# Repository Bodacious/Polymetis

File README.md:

# Polymetis

A 60-key, low-profile keyboard in the exact HHKB Professional 2 layout, with a one-piece 6.25u space bar, Gateron KS-33 low-profile switches on hot-swap sockets, an RP2040 on the board, and RMK firmware with Vial.

The layout is drawn to scale in [`docs/layout.html`](docs/layout.html): keys are coloured by the finger that presses them, and the modifiers are dark grey to match the body. A rotatable concept model is in [`docs/concept.html`](docs/concept.html).

## At a glance

| | |
|---|---|
| Keys | 60, HHKB Professional 2 |
| Bottom row | 1.25u gap, Alt, Cmd 1.5u, Space 6.25u, Cmd 1.5u, Alt, 2.5u gap |
| Switches | Gateron KS-33 Low Profile 2.0, linear (Red) |
| Sockets | Gateron KS-2P02B01-02 hot-swap |
| Stabilisers | one Gateron low-profile plate-mounted 6.25U under the space bar |
| Controller | RP2040 on the board, USB-C |
| Top plate | 1.2 mm FR4, 14.00 mm switch cut-outs |
| Bottom plate | 1.6 mm FR4 with a notch for the USB-C receptacle |
| Frame | 5.3 mm, printed |
| Firmware | RMK with Vial; base layer and the HHKB Fn layer, plus track controls |

The HHKB Professional 2 bottom row has a 6u space bar and a 1.5u gap on the left. Polymetis uses a 6.25u space bar, which low-profile keycap sets include, and takes the extra 0.25u from the left gap. The right-hand bottom keys sit clear of the RP2040, reset pad and boot button. The space bar is centred 6.875u from the left edge, which is where the boundary between the two index fingers falls when averaged over the three letter rows.

## Parts

| Part | Quantity | Notes |
|---|---|---|
| Gateron KS-33 Low Profile 2.0 switch, linear (Red) | 60 | 3.0 mm total travel, 1.7 mm to actuation, 50 gf (Gateron drawing); chosen for short travel |
| Gateron KS-2P02B01-02 low-profile hot-swap socket | 60 | JLCPCB lists it as C18212911; zero stock in October 2026, so plan to solder them by hand |
| Gateron low-profile plate-mounted stabiliser, 6.25U (KS-57B623T) | 1 | sold in a 60% set with four 2U; only the 6.25U is used |
| Main PCB, 1.6 mm, with JLCPCB assembly | 1 | files in `jlcpcb/` |
| Top plate, 1.2 mm FR4 | 1 | `top-plate/` |
| Bottom plate, 1.6 mm FR4 | 1 | `bottom-plate/` |
| Printed middle frame, 5.3 mm | 1 | `case/polymetis-frame.stl` |
| Rubber feet | 4 | tall enough for your USB-C plug: half the plug's thickness minus 2 mm (see `docs/checks/pre-order-verification.md`) |
| M2 screws and nuts | 8 | through top plate, frame and bottom plate (8.1 mm stack) |
| Low-profile keycaps with a cross (MX) stem | 60 | 51 × 1u, 4 × 1.5u, 2 × 1.75u, 2 × 2.25u, 1 × 6.25u |

When ordering FR4 plates from JLCPCB, pay the small extra to leave the order number off.

Gateron's datasheets for the switch, socket and stabilisers are in [`docs/datasheets/`](docs/datasheets/), with a note of what each drawing confirms.

## Stack height

All figures in millimetres, from Gateron's drawings unless marked.

| Layer | Thickness | Source |
|---|---|---|
| Top plate | 1.20 | KS-33 drawing: plate 1.20 ± 0.05 |
| Gap, plate to PCB | 1.30 | KS-33 drawing: plate top to PCB top 2.50 ± 0.05 |
| PCB | 1.60 | |
| Tallest part below the PCB | 2.16 | flash U4, SOIC-8 208-mil, maximum height (Winbond W25Q16JV datasheet) |
| Clearance | 0.24 | |
| **Frame** | **5.30** | gap + PCB + tallest part + clearance |
| Bottom plate | 1.60 | |

The hot-swap sockets are 1.87 below the PCB (KS-2P02B01-02 drawing, ± 0.05) and the reset button 1.5 (XKB TS-1187A); the flash chip is the tallest at 1.95 nominal, 2.16 maximum. The exception is the USB-C receptacle (HRO TYPE-C-31-M-12), which stands 3.26 above the PCB surface it is mounted on. It sits in the frame's USB opening, and the bottom plate has a matching 16 × 13.7 mm notch below it. The stabiliser housing reaches 0.35 below the PCB through its slots.

The frame cavity is cut from the PCB outline plus 0.3 mm.

## The space bar stabiliser

The Gateron 6.25U stabiliser housings reach 3.25 mm below the top plate, more than the 1.30 mm gap, so the PCB has a slot under each housing. Gateron does not publish PCB slot dimensions. The slots here are 6.5 × 16 mm at 100 mm spacing, the size Keebio uses for this stabiliser, centred on the stems and offset 1.8 mm towards the wire-hook side. The top plate uses Gateron's recommended cut-out (6.00 × 12.50 mm housing openings with a 1.70 mm notch, and the 2.50 mm wire groove between them), measured from Gateron's drawing.

The space bar row is only 7.9 mm from the PCB's front edge, so the stabiliser is turned with its notch and wire hooks towards the back of the keyboard; the plate cut-out and the PCB slots both face that way.

**Test-fit before ordering the main PCB.** Order the top plate first (it is cheap), fit the stabiliser and a KS-33 switch, and check that the housings and wire sit within the PCB slot outline in `pcb/local.pretty/STAB_Gateron_LP_6.25U_PCB.kicad_mod`. Enter and left Shift have no stabilisers by design.

## Assembly notes

- Fit the stabiliser in the top plate with its notch towards the back of the keyboard.
- The bottom plate's "Polymetis" text faces outwards (down). The USB notch then lines up with the frame's USB opening at the back right.
- Sockets go on the underside of the PCB, the same side as the RP2040 and diodes. Switches go in from the top through the plate.

## Firmware

RMK 0.5 with Vial, in `firmware/`. Layer 0 is the HHKB Professional 2 base layer. Layer 1 replicates the HHKB Professional 2 Fn layer, plus track controls and a bootloader key on keys the HHKB leaves unused. Hold Fn (right of right Shift) and press

| Keys | Function |
|---|---|
| Esc | Power |
| `1` … `=` | F1 … F12 |
| `\` / `` ` `` | Insert / Delete |
| Tab | Caps Lock |
| `I` `O` `P` | Print Screen, Scroll Lock, Pause |
| `[` | Up |
| Backspace | Backspace |
| `A` `S` `D` | Volume down, volume up, mute |
| `F` | Eject (the HHKB's Mac-mode key) |
| `H` `J` | Keypad `*`, keypad `/` |
| `K` `L` | Home, Page Up |
| `;` `'` | Left, right |
| Enter | Keypad Enter |
| `N` `M` | Keypad `+`, keypad `-` |
| `,` `.` | End, Page Down |
| `/` | Down |
| `Z` `X` `C` | Previous track, play/pause, next track (not on the HHKB) |
| `B` | Bootloader, for flashing (not on the HHKB) |

Any key can be remapped live from the Vial app (or vial.rocks in Chrome), with no rebuild.

### Building and flashing

1. Install Rust with [rustup](https://rustup.rs) (the repo pins the toolchain) and cargo-make: `cargo install cargo-make`.
2. From `firmware/`, run `cargo make uf2`. It builds the firmware and writes `polymetis.uf2`.
3. The first time, hold the board's boot button while plugging in USB. Later, press Fn + B instead. The keyboard appears as a USB drive called RPI-RP2.
4. Copy `polymetis.uf2` onto that drive. The keyboard restarts with the new firmware.

`firmware/README.md` covers flashing with a debug probe instead.

## Design files

| Path | Contents |
|---|---|
| `pcb/` | Main PCB, KiCad 9 (`polymetis.kicad_pro`) |
| `pcb/marbastlib-xp-gateron_lp.pretty` | KS-33 footprints from marbastlib |
| `jlcpcb/` | Main PCB Gerbers, drill files, BOM and placement files for JLCPCB |
| `top-plate/`, `bottom-plate/` | Plate projects and factory files |
| `case/` | Frame: `make_frame.py` and `polymetis-frame.stl`, built from `frame-source.stl` |
| `firmware/` | RMK firmware, `keyboard.toml` and `vial.json` |
| `polymetis.json` | Keyboard Layout Editor description |
| `docs/` | Layout and concept pages, datasheets, ERC/DRC reports and renders |

## Credits

- [ebastler/marbastlib](https://github.com/ebastler/marbastlib) for the KS-33 hot-swap footprints and socket 3D model (CERN-OHL-P-2.0, licence in `pcb/marbastlib-xp-gateron_lp.pretty/LICENSE`).
- [Keebio](https://github.com/keebio/Keebio-Parts.pretty) for the Gateron low-profile stabiliser PCB slot size (MIT).
- [RMK](https://github.com/haobogu/rmk) firmware.
- Gateron for the switch, socket and stabiliser drawings.

## Licence

MIT; see [`LICENSE`](LICENSE).

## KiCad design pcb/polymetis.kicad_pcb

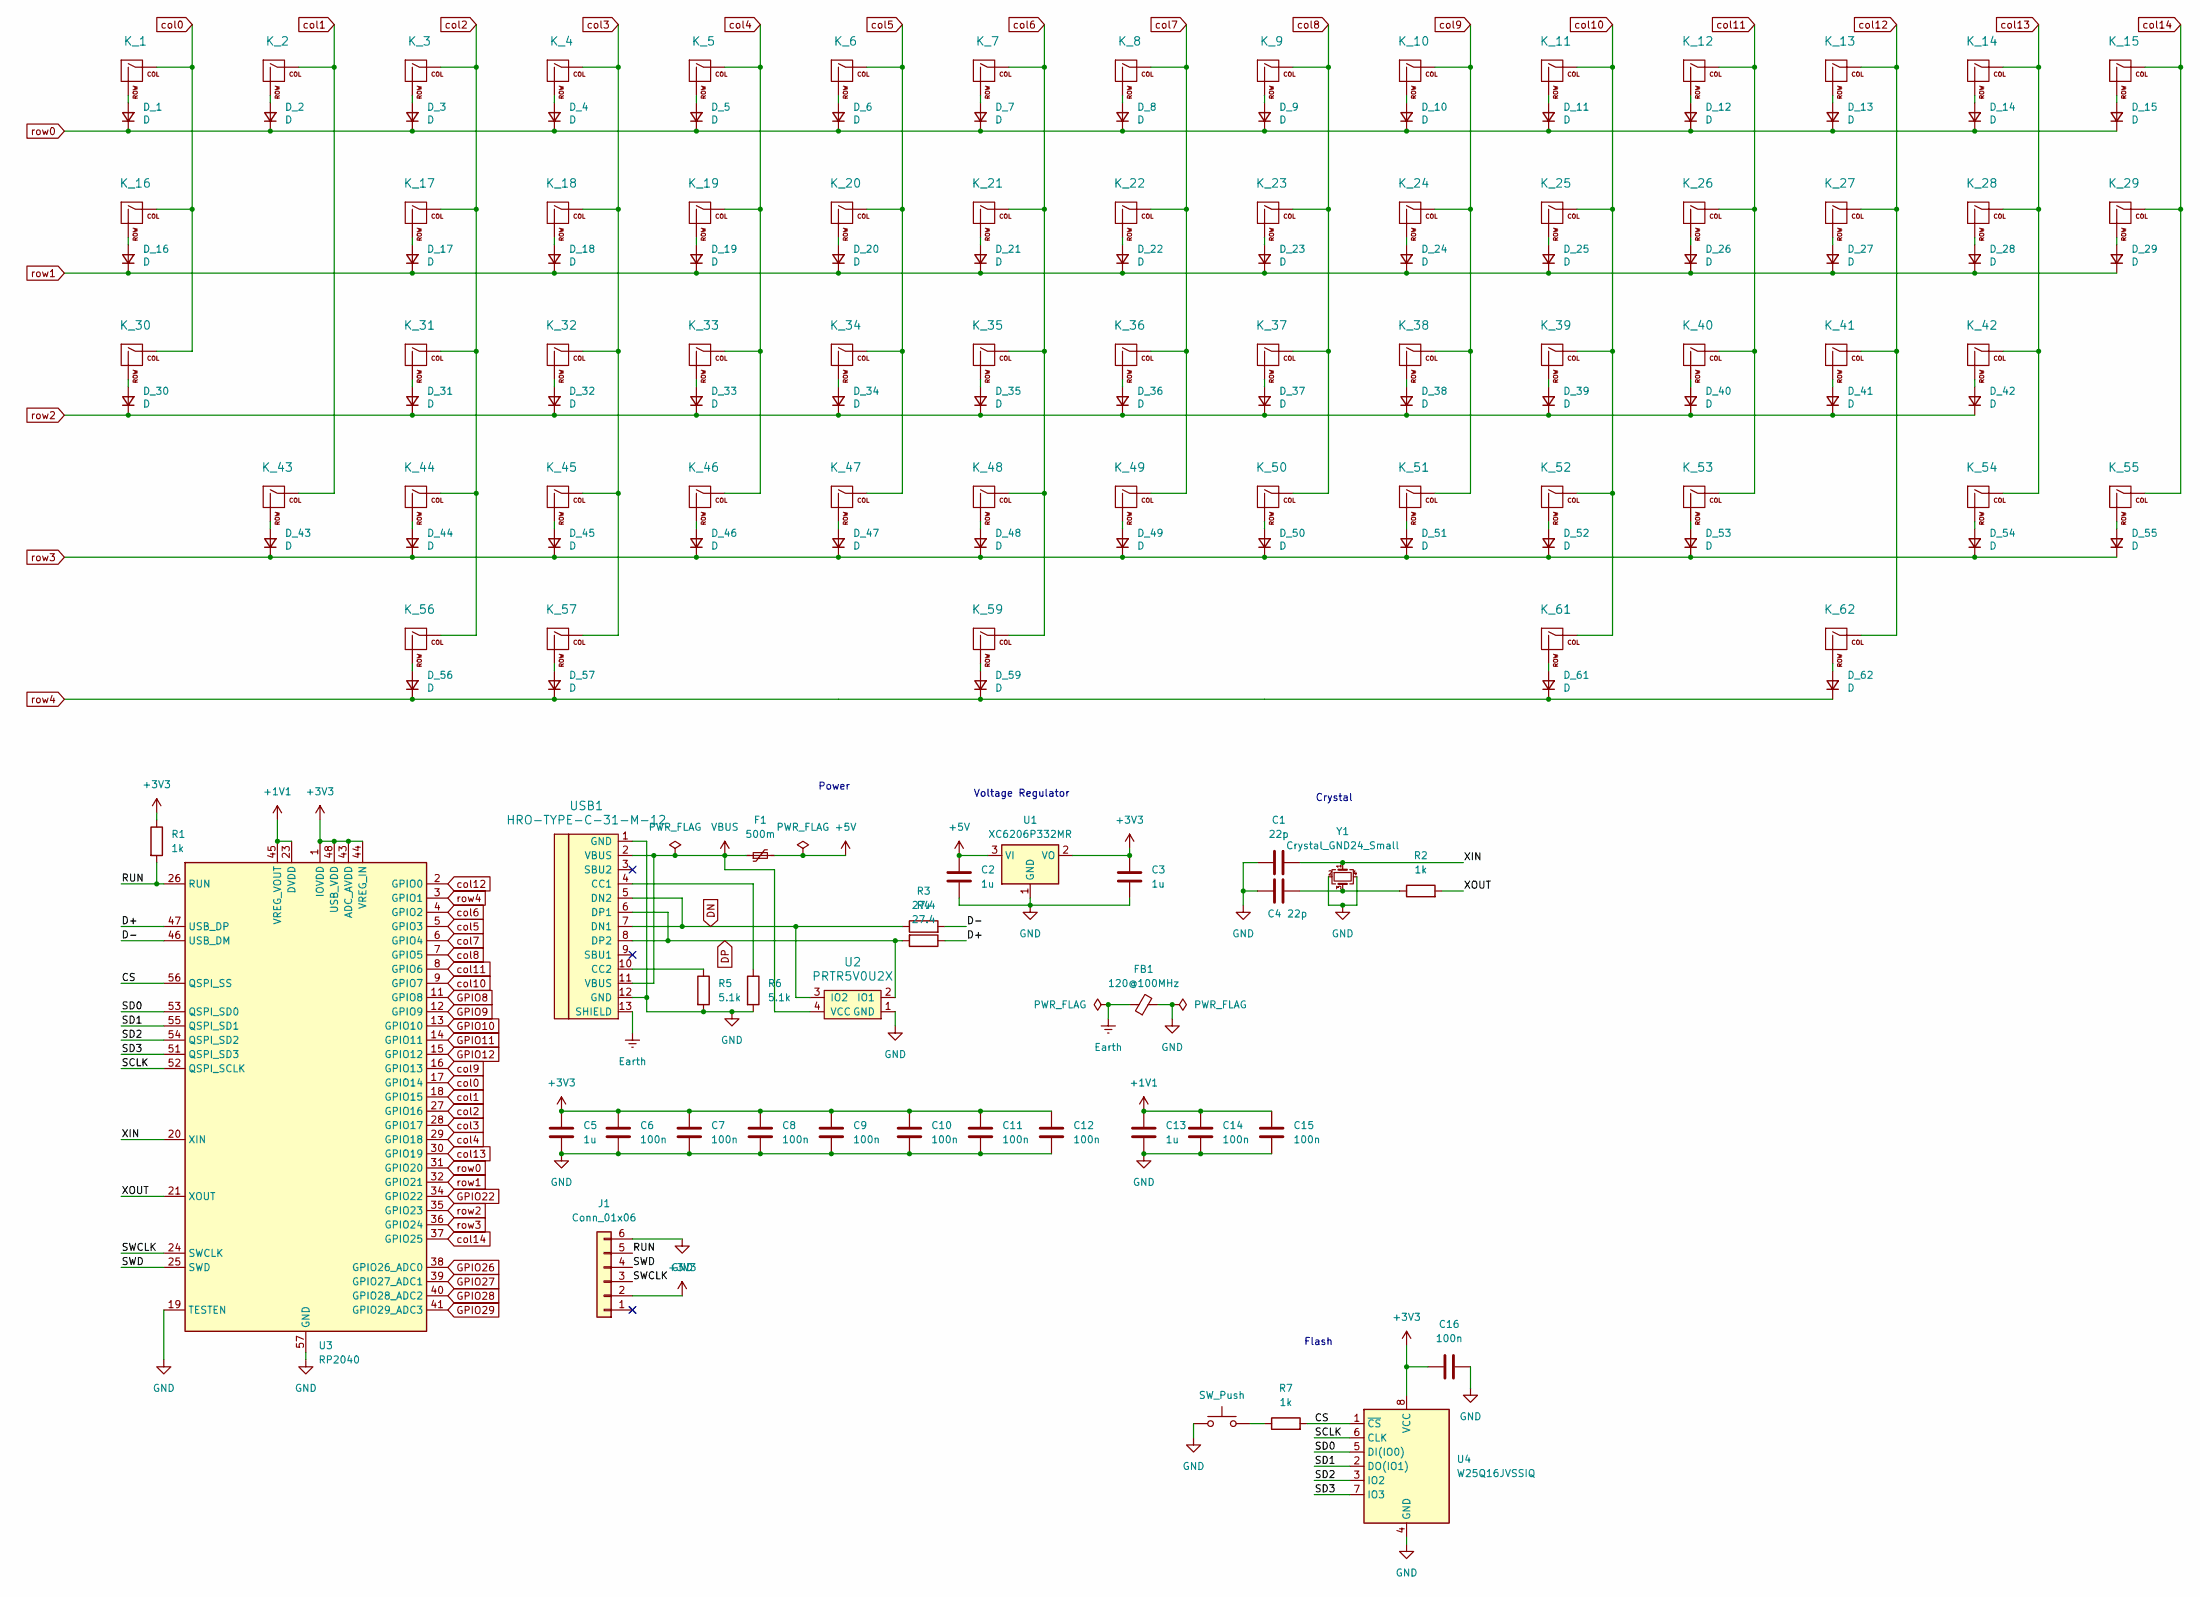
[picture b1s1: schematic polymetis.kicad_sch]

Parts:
C1, C4: 22p; C_0402_1005Metric; JLCPCB Part C1555
C2, C3, C5, C13: 1u; C_0402_1005Metric; JLCPCB Part C52923
C6, C7, C8, C9, C10, C11, C12, C14, C15, C16: 100n; C_0402_1005Metric; JLCPCB Part C1525
D_1, D_2, D_3, D_4, D_5, D_6, D_7, D_8, D_9, D_10, D_11, D_12, D_13, D_14, D_15, D_16, D_17, D_18, D_19, D_20, D_21, D_22, D_23, D_24, D_25, D_26, D_27, D_28, D_29, D_30, D_31, D_32, D_33, D_34, D_35, D_36, D_37, D_38, D_39, D_40, D_41, D_42, D_43, D_44, D_45, D_46, D_47, D_48, D_49, D_50, D_51, D_52, D_53, D_54, D_55, D_56, D_57, D_59, D_61, D_62: D; D_SOD-323; JLCPCB Part C2128
F1: 500m; Fuse_0805_2012Metric; JLCPCB Part C90129
FB1: 120@100MHz; L_0603_1608Metric; JLCPCB Part C14709
J1: Conn_01x06; Reset_Pretty-Mask_rp2040
K_1: esc; SW_KS33_HS_KS-2P02B01-02_HS_1u
K_2: 1; SW_KS33_HS_KS-2P02B01-02_HS_1u
K_3: 2; SW_KS33_HS_KS-2P02B01-02_HS_1u
K_4: 3; SW_KS33_HS_KS-2P02B01-02_HS_1u
K_5: 4; SW_KS33_HS_KS-2P02B01-02_HS_1u
K_6: 5; SW_KS33_HS_KS-2P02B01-02_HS_1u
K_7: 6; SW_KS33_HS_KS-2P02B01-02_HS_1u
K_8: 7; SW_KS33_HS_KS-2P02B01-02_HS_1u
K_9: 8; SW_KS33_HS_KS-2P02B01-02_HS_1u
K_10: 9; SW_KS33_HS_KS-2P02B01-02_HS_1u
K_11: 0; SW_KS33_HS_KS-2P02B01-02_HS_1u
K_12: minus; SW_KS33_HS_KS-2P02B01-02_HS_1u
K_13: equals; SW_KS33_HS_KS-2P02B01-02_HS_1u
K_14: bash; SW_KS33_HS_KS-2P02B01-02_HS_1u
K_15: grave; SW_KS33_HS_KS-2P02B01-02_HS_1u
K_16: tab; SW_KS33_HS_KS-2P02B01-02_1.5u
K_17: q; SW_KS33_HS_KS-2P02B01-02_HS_1u
K_18: w; SW_KS33_HS_KS-2P02B01-02_HS_1u
K_19: e; SW_KS33_HS_KS-2P02B01-02_HS_1u
K_20: r; SW_KS33_HS_KS-2P02B01-02_HS_1u
K_21: t; SW_KS33_HS_KS-2P02B01-02_HS_1u
K_22: y; SW_KS33_HS_KS-2P02B01-02_HS_1u
K_23: u; SW_KS33_HS_KS-2P02B01-02_HS_1u
K_24: i; SW_KS33_HS_KS-2P02B01-02_HS_1u
K_25: o; SW_KS33_HS_KS-2P02B01-02_HS_1u
K_26: p; SW_KS33_HS_KS-2P02B01-02_HS_1u
K_27: l_brace; SW_KS33_HS_KS-2P02B01-02_HS_1u
K_28: r_brace; SW_KS33_HS_KS-2P02B01-02_HS_1u
K_29: bksp; SW_KS33_HS_KS-2P02B01-02_1.5u
K_30: l_ctrl; SW_KS33_HS_KS-2P02B01-02_1.75u
K_31: a; SW_KS33_HS_KS-2P02B01-02_HS_1u
K_32: s; SW_KS33_HS_KS-2P02B01-02_HS_1u
K_33: d; SW_KS33_HS_KS-2P02B01-02_HS_1u
K_34: f; SW_KS33_HS_KS-2P02B01-02_HS_1u
K_35: g; SW_KS33_HS_KS-2P02B01-02_HS_1u
K_36: h; SW_KS33_HS_KS-2P02B01-02_HS_1u
K_37: j; SW_KS33_HS_KS-2P02B01-02_HS_1u
K_38: k; SW_KS33_HS_KS-2P02B01-02_HS_1u
K_39: l; SW_KS33_HS_KS-2P02B01-02_HS_1u
K_40: semi; SW_KS33_HS_KS-2P02B01-02_HS_1u
K_41: quote; SW_KS33_HS_KS-2P02B01-02_HS_1u
K_42: enter; SW_KS33_HS_KS-2P02B01-02_HS_1u
K_43: l_shift; SW_KS33_HS_KS-2P02B01-02_HS_1u
K_44: z; SW_KS33_HS_KS-2P02B01-02_HS_1u
K_45: x; SW_KS33_HS_KS-2P02B01-02_HS_1u
K_46: c; SW_KS33_HS_KS-2P02B01-02_HS_1u
K_47: v; SW_KS33_HS_KS-2P02B01-02_HS_1u
K_48: b; SW_KS33_HS_KS-2P02B01-02_HS_1u
K_49: n; SW_KS33_HS_KS-2P02B01-02_HS_1u
K_50: m; SW_KS33_HS_KS-2P02B01-02_HS_1u
K_51: comma; SW_KS33_HS_KS-2P02B01-02_HS_1u
K_52: dot; SW_KS33_HS_KS-2P02B01-02_HS_1u
K_53: slash; SW_KS33_HS_KS-2P02B01-02_HS_1u
K_54: r_shift; SW_KS33_HS_KS-2P02B01-02_1.75u
K_55: mo1; SW_KS33_HS_KS-2P02B01-02_HS_1u
K_56: l_gui; SW_KS33_HS_KS-2P02B01-02_HS_1u
K_57: l_alt; SW_KS33_HS_KS-2P02B01-02_1.5u
K_59: mo2; SW_KS33_HS_KS-2P02B01-02_HS_1u
K_61: r_alt; SW_KS33_HS_KS-2P02B01-02_1.5u
K_62: r_ctrl; SW_KS33_HS_KS-2P02B01-02_HS_1u
R1, R2, R7: 1k; R_0402_1005Metric; JLCPCB Part C11702
R3, R4: 27.4; R_0402_1005Metric; JLCPCB Part C274349
R5, R6: 5.1k; R_0402_1005Metric; JLCPCB Part C25905
SW1: SW_Push; SW_SPST_SKQG_WithStem; JLCPCB Part C318884
U1: XC6206P332MR; SOT-23-3; JLCPCB Part C5446
U2: PRTR5V0U2X; SOT-143; JLCPCB Part C2827688
U3: RP2040; QFN-56-1EP_7x7mm_P0.4mm_EP3.2x3.2mm; JLCPCB Part C2040
U4: W25Q16JVSSIQ; SOIC-8_5.23x5.23mm_P1.27mm; JLCPCB Part C131025
USB1: HRO-TYPE-C-31-M-12; HRO-TYPE-C-31-M-12-HandSoldering; JLCPCB Part C165948
Y1: Crystal_GND24_Small; Crystal_SMD_3225-4Pin_3.2x2.5mm; JLCPCB Part C9002

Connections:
+1V1: C13.1, C14.1, C15.1, U3.23 (DVDD), U3.45 (VREG_VOUT), U3.50 (DVDD)
+3V3: C3.1, C5.1, C6.1, C7.1, C8.1, C9.1, C10.1, C11.1, C12.1, C16.1, J1.2, R1.1, U1.2 (VO), U3.1 (IOVDD), U3.10 (IOVDD), U3.22 (IOVDD), U3.33 (IOVDD), U3.42 (IOVDD), U3.43 (ADC_AVDD), U3.44 (VREG_IN), U3.48 (USB_VDD), U3.49 (IOVDD), U4.8 (VCC)
+5V: C2.1, F1.2, U1.3 (VI)
/CS: R7.2, U3.56 (QSPI_SS), U4.1 (~CS)
/D+: R4.1, U3.47 (USB_DP)
/D-: R3.2, U3.46 (USB_DM)
/RUN: J1.5, R1.2, U3.26 (RUN)
/SCLK: U3.52 (QSPI_SCLK), U4.6 (CLK)
/SD0: U3.53 (QSPI_SD0), U4.5 (DI(IO0))
/SD1: U3.55 (QSPI_SD1), U4.2 (DO(IO1))
/SD2: U3.54 (QSPI_SD2), U4.3 (IO2)
/SD3: U3.51 (QSPI_SD3), U4.7 (IO3)
/SWCLK: J1.3, U3.24 (SWCLK)
/SWD: J1.4, U3.25 (SWD)
/XIN: C1.2, U3.20 (XIN), Y1.1
/XOUT: R2.2, U3.21 (XOUT)
DN: R3.1, U2.3 (IO2), USB1.5 (DN2), USB1.7 (DN1)
DP: R4.2, U2.2 (IO1), USB1.6 (DP1), USB1.8 (DP2)
Earth: FB1.1, USB1.13 (SHIELD)
GND: C1.1, C2.2, C3.2, C4.1, C5.2, C6.2, C7.2, C8.2, C9.2, C10.2, C11.2, C12.2, C13.2, C14.2, C15.2, C16.2, FB1.2, J1.6, R5.2, R6.2, SW1.1, U1.1 (GND), U2.1 (GND), U3.19 (TESTEN), U3.57 (GND), U4.4 (GND), USB1.1 (GND), USB1.12 (GND), Y1.2, Y1.4
GPIO8: U3.11 (GPIO8)
GPIO9: U3.12 (GPIO9)
GPIO10: U3.13 (GPIO10)
GPIO11: U3.14 (GPIO11)
GPIO12: U3.15 (GPIO12)
GPIO22: U3.34 (GPIO22)
GPIO26: U3.38 (GPIO26_ADC0)
GPIO27: U3.39 (GPIO27_ADC1)
GPIO28: U3.40 (GPIO28_ADC2)
GPIO29: U3.41 (GPIO29_ADC3)
unnamed: C4.2, R2.1, Y1.3
unnamed: D_1.2 (A), K_1.2 (ROW)
unnamed: D_2.2 (A), K_2.2 (ROW)
unnamed: D_3.2 (A), K_3.2 (ROW)
unnamed: D_4.2 (A), K_4.2 (ROW)
unnamed: D_5.2 (A), K_5.2 (ROW)
unnamed: D_6.2 (A), K_6.2 (ROW)
unnamed: D_7.2 (A), K_7.2 (ROW)
unnamed: D_8.2 (A), K_8.2 (ROW)
unnamed: D_9.2 (A), K_9.2 (ROW)
unnamed: D_10.2 (A), K_10.2 (ROW)
unnamed: D_11.2 (A), K_11.2 (ROW)
unnamed: D_12.2 (A), K_12.2 (ROW)
unnamed: D_13.2 (A), K_13.2 (ROW)
unnamed: D_14.2 (A), K_14.2 (ROW)
unnamed: D_15.2 (A), K_15.2 (ROW)
unnamed: D_16.2 (A), K_16.2 (ROW)
unnamed: D_17.2 (A), K_17.2 (ROW)
unnamed: D_18.2 (A), K_18.2 (ROW)
unnamed: D_19.2 (A), K_19.2 (ROW)
unnamed: D_20.2 (A), K_20.2 (ROW)
unnamed: D_21.2 (A), K_21.2 (ROW)
unnamed: D_22.2 (A), K_22.2 (ROW)
unnamed: D_23.2 (A), K_23.2 (ROW)
unnamed: D_24.2 (A), K_24.2 (ROW)
unnamed: D_25.2 (A), K_25.2 (ROW)
unnamed: D_26.2 (A), K_26.2 (ROW)
unnamed: D_27.2 (A), K_27.2 (ROW)
unnamed: D_28.2 (A), K_28.2 (ROW)
unnamed: D_29.2 (A), K_29.2 (ROW)
unnamed: D_30.2 (A), K_30.2 (ROW)
unnamed: D_31.2 (A), K_31.2 (ROW)
unnamed: D_32.2 (A), K_32.2 (ROW)
unnamed: D_33.2 (A), K_33.2 (ROW)
unnamed: D_34.2 (A), K_34.2 (ROW)
unnamed: D_35.2 (A), K_35.2 (ROW)
unnamed: D_36.2 (A), K_36.2 (ROW)
unnamed: D_37.2 (A), K_37.2 (ROW)
unnamed: D_38.2 (A), K_38.2 (ROW)
unnamed: D_39.2 (A), K_39.2 (ROW)
unnamed: D_40.2 (A), K_40.2 (ROW)
unnamed: D_41.2 (A), K_41.2 (ROW)
unnamed: D_42.2 (A), K_42.2 (ROW)
unnamed: D_43.2 (A), K_43.2 (ROW)
unnamed: D_44.2 (A), K_44.2 (ROW)
unnamed: D_45.2 (A), K_45.2 (ROW)
unnamed: D_46.2 (A), K_46.2 (ROW)
unnamed: D_47.2 (A), K_47.2 (ROW)
unnamed: D_48.2 (A), K_48.2 (ROW)
unnamed: D_49.2 (A), K_49.2 (ROW)
unnamed: D_50.2 (A), K_50.2 (ROW)
unnamed: D_51.2 (A), K_51.2 (ROW)
unnamed: D_52.2 (A), K_52.2 (ROW)
unnamed: D_53.2 (A), K_53.2 (ROW)
unnamed: D_54.2 (A), K_54.2 (ROW)
unnamed: D_55.2 (A), K_55.2 (ROW)
unnamed: D_56.2 (A), K_56.2 (ROW)
unnamed: D_57.2 (A), K_57.2 (ROW)
unnamed: D_59.2 (A), K_59.2 (ROW)
unnamed: D_61.2 (A), K_61.2 (ROW)
unnamed: D_62.2 (A), K_62.2 (ROW)
unnamed: R7.1, SW1.2
unnamed: R6.1, USB1.4 (CC1)
unnamed: R5.1, USB1.10 (CC2)
VBUS: F1.1, U2.4 (VCC), USB1.2 (VBUS), USB1.11 (VBUS)
col0: K_1.1 (COL), K_16.1 (COL), K_30.1 (COL), U3.17 (GPIO14)
col1: K_2.1 (COL), K_43.1 (COL), U3.18 (GPIO15)
col2: K_3.1 (COL), K_17.1 (COL), K_31.1 (COL), K_44.1 (COL), K_56.1 (COL), U3.27 (GPIO16)
col3: K_4.1 (COL), K_18.1 (COL), K_32.1 (COL), K_45.1 (COL), K_57.1 (COL), U3.28 (GPIO17)
col4: K_5.1 (COL), K_19.1 (COL), K_33.1 (COL), K_46.1 (COL), U3.29 (GPIO18)
col5: K_6.1 (COL), K_20.1 (COL), K_34.1 (COL), K_47.1 (COL), U3.5 (GPIO3)
col6: K_7.1 (COL), K_21.1 (COL), K_35.1 (COL), K_48.1 (COL), K_59.1 (COL), U3.4 (GPIO2)
col7: K_8.1 (COL), K_22.1 (COL), K_36.1 (COL), K_49.1 (COL), U3.6 (GPIO4)
col8: K_9.1 (COL), K_23.1 (COL), K_37.1 (COL), K_50.1 (COL), U3.7 (GPIO5)
col9: K_10.1 (COL), K_24.1 (COL), K_38.1 (COL), K_51.1 (COL), U3.16 (GPIO13)
col10: K_11.1 (COL), K_25.1 (COL), K_39.1 (COL), K_52.1 (COL), K_61.1 (COL), U3.9 (GPIO7)
col11: K_12.1 (COL), K_26.1 (COL), K_40.1 (COL), K_53.1 (COL), U3.8 (GPIO6)
col12: K_13.1 (COL), K_27.1 (COL), K_41.1 (COL), K_62.1 (COL), U3.2 (GPIO0)
col13: K_14.1 (COL), K_28.1 (COL), K_42.1 (COL), K_54.1 (COL), U3.30 (GPIO19)
col14: K_15.1 (COL), K_29.1 (COL), K_55.1 (COL), U3.37 (GPIO25)
row0: D_1.1 (K), D_2.1 (K), D_3.1 (K), D_4.1 (K), D_5.1 (K), D_6.1 (K), D_7.1 (K), D_8.1 (K), D_9.1 (K), D_10.1 (K), D_11.1 (K), D_12.1 (K), D_13.1 (K), D_14.1 (K), D_15.1 (K), U3.31 (GPIO20)
row1: D_16.1 (K), D_17.1 (K), D_18.1 (K), D_19.1 (K), D_20.1 (K), D_21.1 (K), D_22.1 (K), D_23.1 (K), D_24.1 (K), D_25.1 (K), D_26.1 (K), D_27.1 (K), D_28.1 (K), D_29.1 (K), U3.32 (GPIO21)
row2: D_30.1 (K), D_31.1 (K), D_32.1 (K), D_33.1 (K), D_34.1 (K), D_35.1 (K), D_36.1 (K), D_37.1 (K), D_38.1 (K), D_39.1 (K), D_40.1 (K), D_41.1 (K), D_42.1 (K), U3.35 (GPIO23)
row3: D_43.1 (K), D_44.1 (K), D_45.1 (K), D_46.1 (K), D_47.1 (K), D_48.1 (K), D_49.1 (K), D_50.1 (K), D_51.1 (K), D_52.1 (K), D_53.1 (K), D_54.1 (K), D_55.1 (K), U3.36 (GPIO24)
row4: D_56.1 (K), D_57.1 (K), D_59.1 (K), D_61.1 (K), D_62.1 (K), U3.3 (GPIO1)

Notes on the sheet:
Flash
Power
Crystal
Voltage Regulator

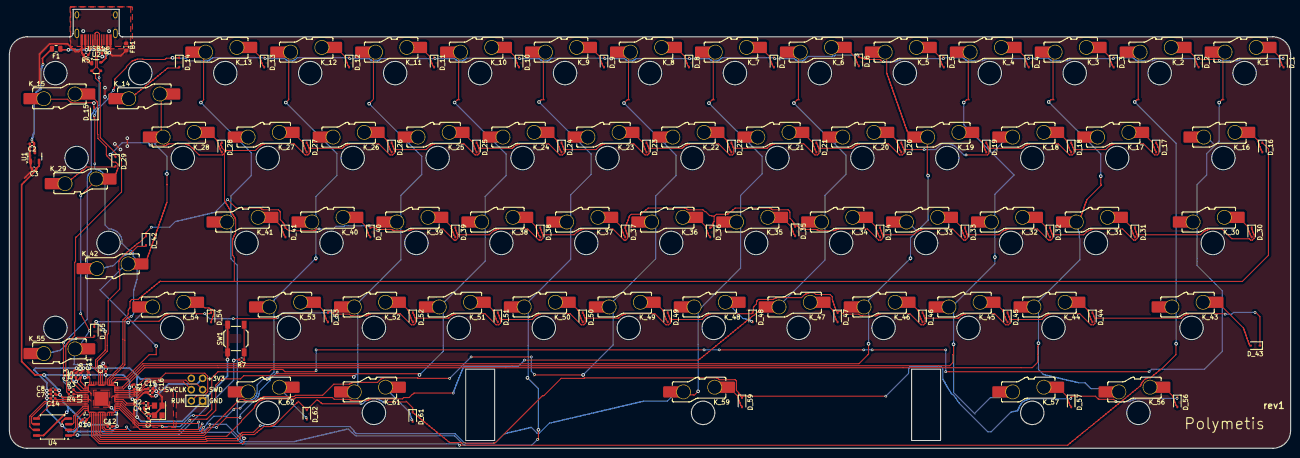
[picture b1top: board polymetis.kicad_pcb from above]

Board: 2 copper layers, 287.3 x 98.4 mm, 154 parts (0 on the bottom side), 105 nets.

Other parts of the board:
ST1: KS-57B623T; STAB_Gateron_LP_6.25U_PCB
